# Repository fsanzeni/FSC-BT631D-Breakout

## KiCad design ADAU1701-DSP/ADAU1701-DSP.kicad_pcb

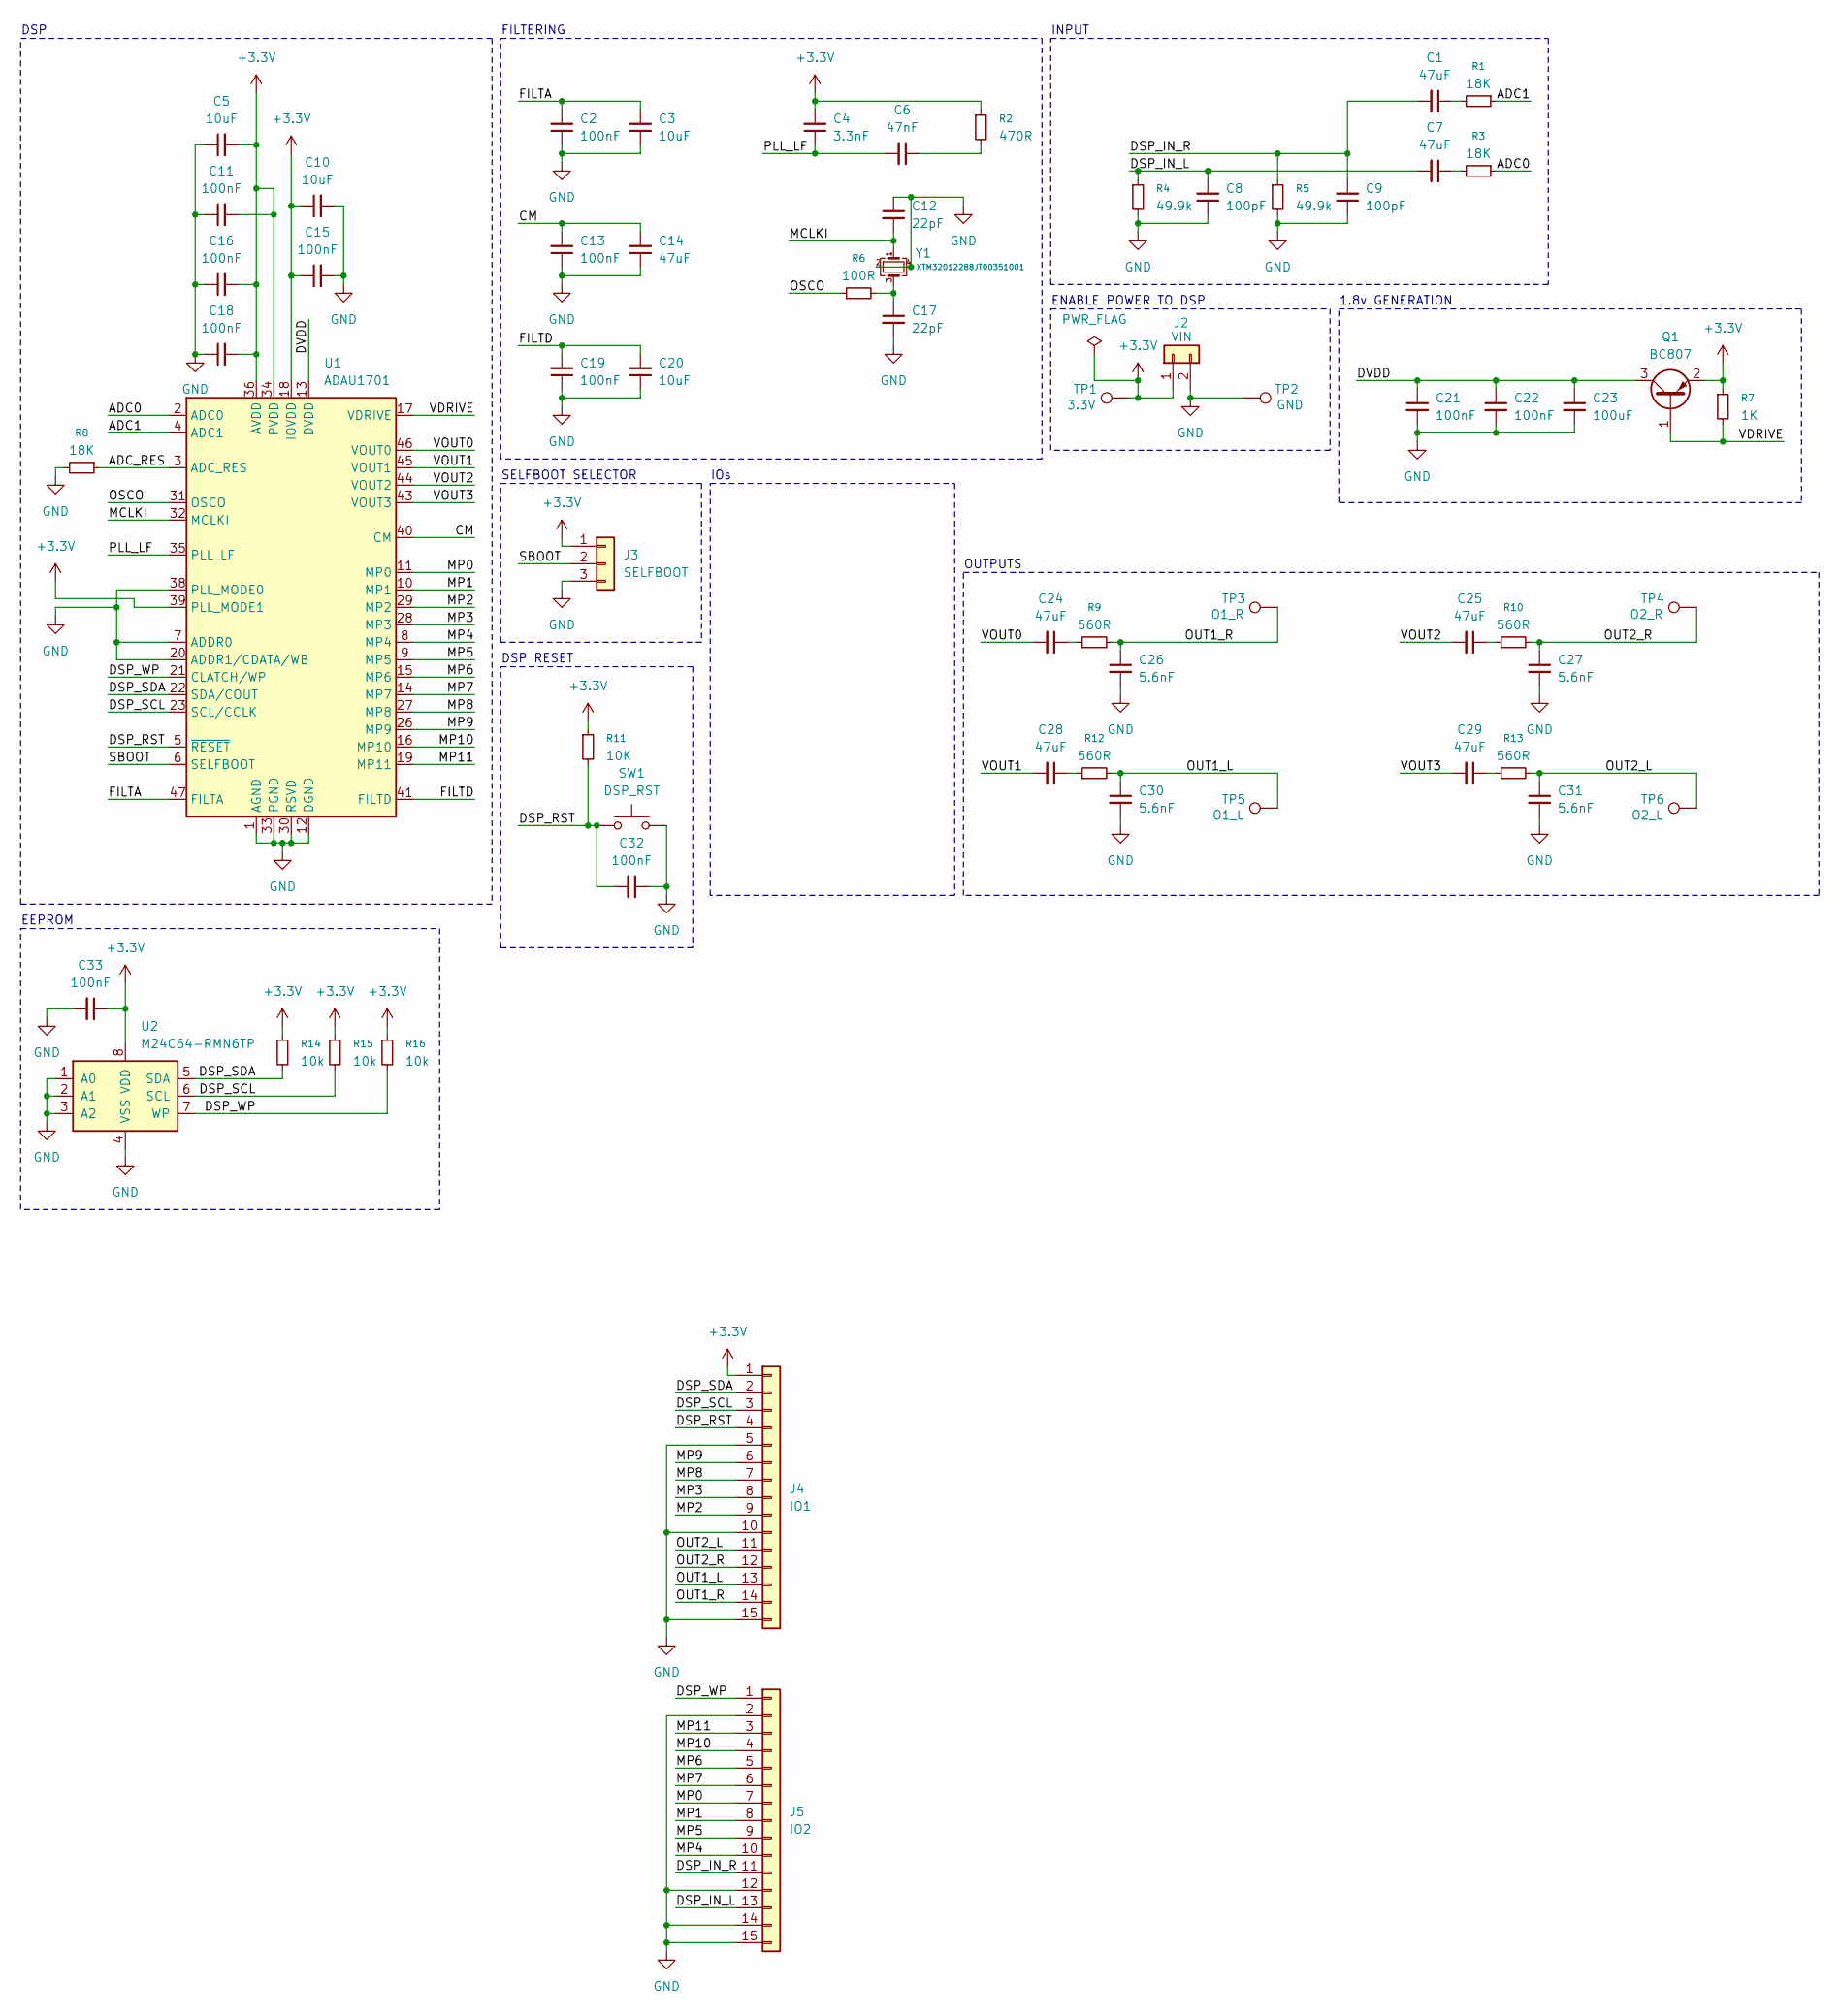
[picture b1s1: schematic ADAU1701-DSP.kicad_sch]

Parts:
C1, C7, C14, C24, C25, C28, C29: 47uF; C_0603_1608Metric_Pad1.08x0.95mm_HandSolder
C2, C11, C13, C15, C16, C18, C19, C21, C22, C32, C33: 100nF; C_0603_1608Metric_Pad1.08x0.95mm_HandSolder
C3, C5, C10, C20: 10uF; C_0603_1608Metric_Pad1.08x0.95mm_HandSolder
C4: 3.3nF; C_0603_1608Metric_Pad1.08x0.95mm_HandSolder
C6: 47nF; C_0603_1608Metric_Pad1.08x0.95mm_HandSolder
C8, C9: 100pF; C_0603_1608Metric_Pad1.08x0.95mm_HandSolder
C12, C17: 22pF; C_0603_1608Metric_Pad1.08x0.95mm_HandSolder
C23: 100uF; C_0603_1608Metric_Pad1.08x0.95mm_HandSolder
C26, C27, C30, C31: 5.6nF; C_0603_1608Metric_Pad1.08x0.95mm_HandSolder
J2: VIN; PinSocket_1x02_P2.54mm_Vertical
J3: SELFBOOT; PinHeader_1x03_P2.54mm_Vertical
J4: IO1; PinSocket_1x15_P2.54mm_Vertical
J5: IO2; PinSocket_1x15_P2.54mm_Vertical
Q1: BC807; SOT-23
R1, R3, R8: 18K; R_0603_1608Metric_Pad0.98x0.95mm_HandSolder
R2: 470R; R_0603_1608Metric_Pad0.98x0.95mm_HandSolder
R4, R5: 49.9k; R_0603_1608Metric_Pad0.98x0.95mm_HandSolder
R6: 100R; R_0603_1608Metric_Pad0.98x0.95mm_HandSolder
R7: 1K; R_0603_1608Metric_Pad0.98x0.95mm_HandSolder
R9, R10, R12, R13: 560R; R_0603_1608Metric_Pad0.98x0.95mm_HandSolder
R11: 10K; R_0603_1608Metric_Pad0.98x0.95mm_HandSolder
R14, R15, R16: 10k; R_0603_1608Metric_Pad0.98x0.95mm_HandSolder
SW1: DSP_RST; TS3425BA
TP1: 3.3V; TestPoint_THTPad_1.0x1.0mm_Drill0.5mm
TP2: GND; TestPoint_THTPad_1.0x1.0mm_Drill0.5mm
TP3: O1_R; TestPoint_THTPad_1.0x1.0mm_Drill0.5mm
TP4: O2_R; TestPoint_THTPad_1.0x1.0mm_Drill0.5mm
TP5: O1_L; TestPoint_THTPad_1.0x1.0mm_Drill0.5mm
TP6: O2_L; TestPoint_THTPad_1.0x1.0mm_Drill0.5mm
U1: ADAU1701; LQFP-48_7x7mm_P0.5mm
U2: M24C64-RMN6TP; SOIC-8_3.9x4.9mm_P1.27mm
Y1: XTM32012288JT00351001; Crystal_SMD_3225-4Pin_3.2x2.5mm_HandSoldering

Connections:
+3.3V: C4.2, C5.2, C10.1, C11.2, C15.1, C16.2, C18.2, C33.1, J2.1, J3.1, J4.1, Q1.2 (E), R2.1, R7.1, R11.1, R14.1, R15.1, R16.1, TP1.1, U1.18 (IOVDD), U1.34 (PVDD), U1.36 (AVDD), U1.39 (PLL_MODE1), U1.48 (AVDD), U2.8 (VDD)
/ADC0: R3.1, U1.2 (ADC0)
/ADC1: R1.1, U1.4 (ADC1)
/ADC_RES: R8.1, U1.3 (ADC_RES)
/CM: C13.2, C14.2, U1.40 (CM)
/DSP_IN_L: C7.2, C8.2, J5.13, R4.1
/DSP_IN_R: C1.2, C9.2, J5.11, R5.1
/DSP_RST: C32.2, J4.4, R11.2, SW1.1, U1.5 (~RESET)
/DSP_SCL: J4.3, R15.2, U1.23 (SCL/CCLK), U2.6 (SCL)
/DSP_SDA: J4.2, R14.2, U1.22 (SDA/COUT), U2.5 (SDA)
/DSP_WP: J5.1, R16.2, U1.21 (CLATCH/WP), U2.7 (WP)
/DVDD: C21.1, C22.1, C23.1, Q1.3 (C), U1.13 (DVDD), U1.24 (DVDD)
/FILTA: C2.2, C3.2, U1.47 (FILTA)
/FILTD: C19.2, C20.2, U1.41 (FILTD)
/MCLKI: C12.2, U1.32 (MCLKI), Y1.1
/MP0: J5.7, U1.11 (MP0)
/MP1: J5.8, U1.10 (MP1)
/MP2: J4.9, U1.29 (MP2)
/MP3: J4.8, U1.28 (MP3)
/MP4: J5.10, U1.8 (MP4)
/MP5: J5.9, U1.9 (MP5)
/MP6: J5.5, U1.15 (MP6)
/MP7: J5.6, U1.14 (MP7)
/MP8: J4.7, U1.27 (MP8)
/MP9: J4.6, U1.26 (MP9)
/MP10: J5.4, U1.16 (MP10)
/MP11: J5.3, U1.19 (MP11)
/OSCO: R6.1, U1.31 (OSCO)
/OUT1_L: C30.1, J4.13, R12.2, TP5.1
/OUT1_R: C26.1, J4.14, R9.2, TP3.1
/OUT2_L: C31.1, J4.11, R13.2, TP6.1
/OUT2_R: C27.1, J4.12, R10.2, TP4.1
/PLL_LF: C4.1, C6.2, U1.35 (PLL_LF)
/SBOOT: J3.2, U1.6 (SELFBOOT)
/VDRIVE: Q1.1 (B), R7.2, U1.17 (VDRIVE)
/VOUT0: C24.2, U1.46 (VOUT0)
/VOUT1: C28.2, U1.45 (VOUT1)
/VOUT2: C25.2, U1.44 (VOUT2)
/VOUT3: C29.2, U1.43 (VOUT3)
GND: C2.1, C3.1, C5.1, C8.1, C9.1, C10.2, C11.1, C12.1, C13.1, C14.1, C15.2, C16.1, C17.2, C18.1, C19.1, C20.1, C21.2, C22.2, C23.2, C26.2, C27.2, C30.2, C31.2, C32.1, C33.2, J2.2, J3.3, J4.5, J4.10, J4.15, J5.2, J5.12, J5.14, J5.15, R4.2, R5.2, R8.2, SW1.2, TP2.1, U1.1 (AGND), U1.7 (ADDR0), U1.12 (DGND), U1.20 (ADDR1/CDATA/WB), U1.25 (DGND), U1.30 (RSVD), U1.33 (PGND), U1.37 (AGND), U1.38 (PLL_MODE0), U1.42 (AGND), U2.1 (A0), U2.2 (A1), U2.3 (A2), U2.4 (VSS), Y1.2, Y1.4
unnamed: C1.1, R1.2
unnamed: C6.1, R2.2
unnamed: C7.1, R3.2
unnamed: C17.1, R6.2, Y1.3
unnamed: C24.1, R9.1
unnamed: C25.1, R10.1
unnamed: C28.1, R12.1
unnamed: C29.1, R13.1

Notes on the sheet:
EEPROM
INPUT
DSP RESET
FILTERING
DSP
IOs
SELFBOOT SELECTOR
ENABLE POWER TO DSP
1.8v GENERATION
OUTPUTS

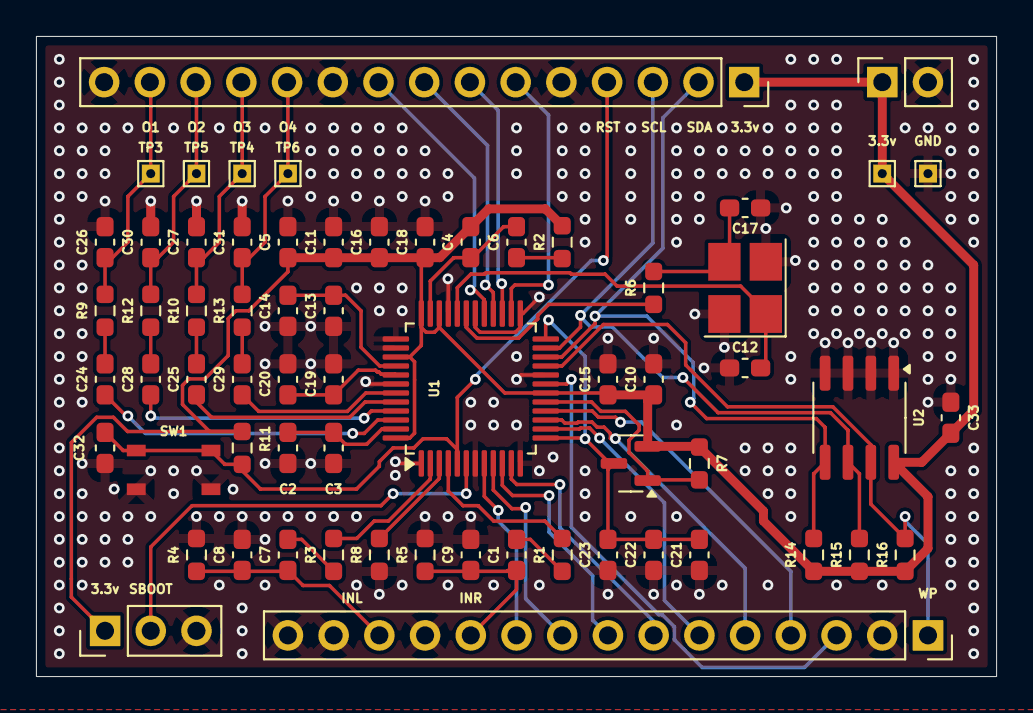
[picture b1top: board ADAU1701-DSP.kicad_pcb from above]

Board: 2 copper layers, 53.3 x 35.6 mm, 64 parts (0 on the bottom side), 48 nets.

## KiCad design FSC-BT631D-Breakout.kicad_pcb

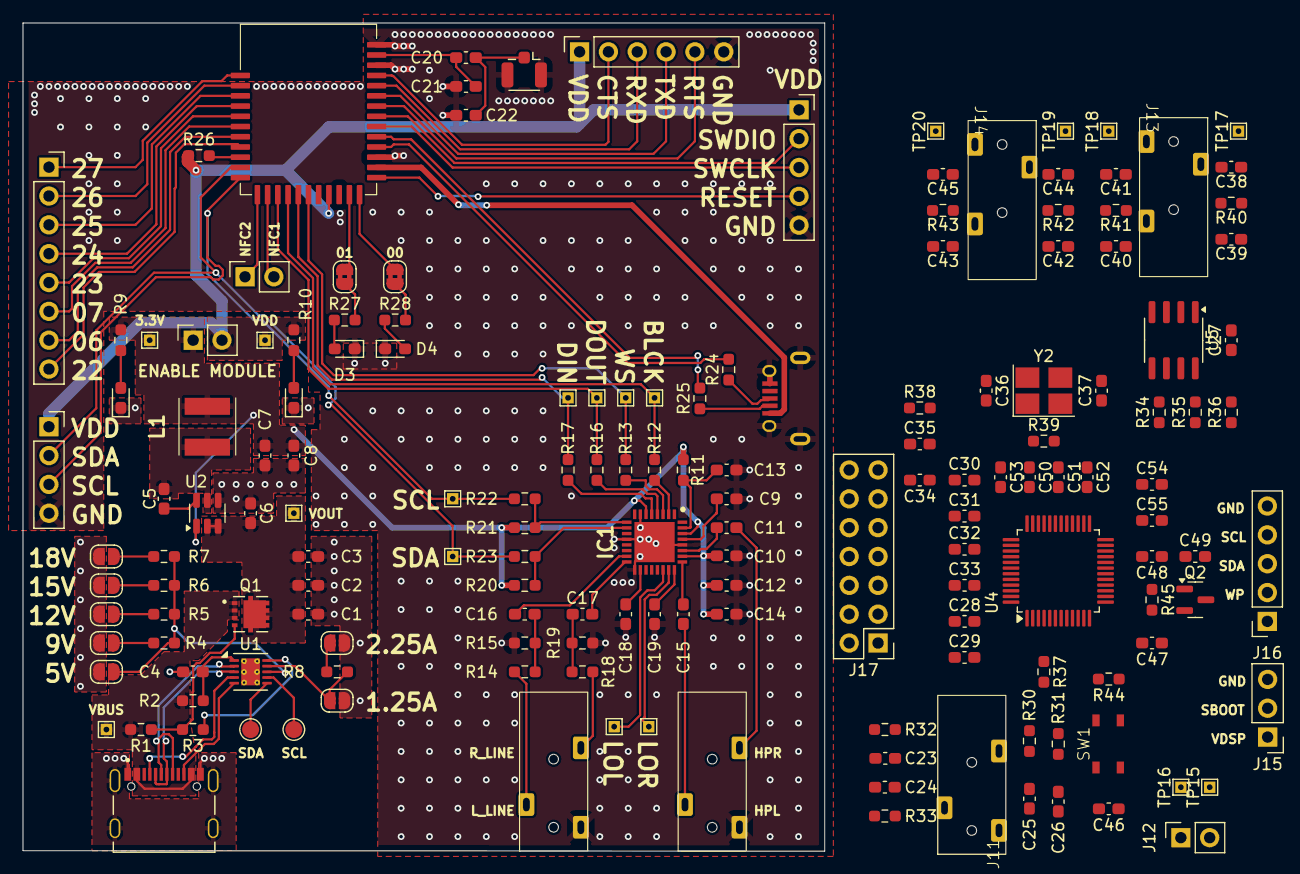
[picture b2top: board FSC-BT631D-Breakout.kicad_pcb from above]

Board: 2 copper layers, 70.6 x 72.9 mm, 161 parts (0 on the bottom side), 128 nets.

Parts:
AE1: Antenna_Shield; U.FL_Hirose_U.FL-R-SMT-1_Vertical
C1, C2, C3, C6, C11, C15, C16, C17, C19: 4.7uF; C_0603_1608Metric_Pad1.08x0.95mm_HandSolder
C4: 1uF/50V; C_0603_1608Metric_Pad1.08x0.95mm_HandSolder
C5: 0.1uF; C_0603_1608Metric_Pad1.08x0.95mm_HandSolder
C7, C8: 22uF; C_0603_1608Metric_Pad1.08x0.95mm_HandSolder
C9, C10, C18, C29, C33, C53, C54: 10uF; C_0603_1608Metric_Pad1.08x0.95mm_HandSolder
C12: 1uF; C_0603_1608Metric_Pad1.08x0.95mm_HandSolder
C13: 220nF; C_0603_1608Metric_Pad1.08x0.95mm_HandSolder
C14, C27, C28, C30, C32, C46, C47, C48, C50, C51, C52, C55: 100nF; C_0603_1608Metric_Pad1.08x0.95mm_HandSolder
C20, C21, C22: NC; C_0603_1608Metric_Pad1.08x0.95mm_HandSolder
C23, C24: 100pF; C_0603_1608Metric_Pad1.08x0.95mm_HandSolder
C25, C26, C31, C39, C40, C42, C43: 47uF; C_0603_1608Metric_Pad1.08x0.95mm_HandSolder
C34: 3.3nF; C_0603_1608Metric_Pad1.08x0.95mm_HandSolder
C35: 47nF; C_0603_1608Metric_Pad1.08x0.95mm_HandSolder
C36, C37: 22pF; C_0603_1608Metric_Pad1.08x0.95mm_HandSolder
C38, C41, C44, C45: 5.6nF; C_0603_1608Metric_Pad1.08x0.95mm_HandSolder
C49: 100uF; C_0603_1608Metric_Pad1.08x0.95mm_HandSolder
D1: 3.3V; LED_0603_1608Metric_Pad1.05x0.95mm_HandSolder
D2: VDD; LED_0603_1608Metric_Pad1.05x0.95mm_HandSolder
D3: LED1; LED_0603_1608Metric_Pad1.05x0.95mm_HandSolder
D4: LED2; LED_0603_1608Metric_Pad1.05x0.95mm_HandSolder
IC1: TLV320AIC3204IRHBR; QFN50P500X500X100-33N-D
J1: USB_C_Receptacle_USB2.0_16P; SHOUHAN_TYPE-C_16PIN_2MD__073
J2: M_EN; PinSocket_1x02_P2.54mm_Vertical
J3: LINE IN; XKB_PJ-3200
J4: LINE OUT; XKB_PJ-3200
J5: USB_B_Micro; KH-MICRO5P-JN
J6: UPDATE; PinSocket_1x05_P2.54mm_Vertical
J7: UART; PinSocket_1x06_P2.54mm_Vertical
J8: I2C; PinSocket_1x04_P2.54mm_Vertical
J9: NFC; PinSocket_1x02_P2.54mm_Vertical
J10: PIO; PinSocket_1x08_P2.54mm_Vertical
J11: DSP IN; XKB_PJ-3200
J12: DSP_EN; PinSocket_1x02_P2.54mm_Vertical
J13: OUT1; XKB_PJ-3200
J14: OUT2; XKB_PJ-3200
J15: SELFBOOT; PinHeader_1x03_P2.54mm_Vertical
J16: DSP_PROG; PinSocket_1x05_P2.54mm_Vertical
J17: DSP_GPIO; PinHeader_2x07_P2.54mm_Vertical
JP1: 5V; SolderJumper-2_P1.3mm_Open_RoundedPad1.0x1.5mm
JP2: 9V; SolderJumper-2_P1.3mm_Open_RoundedPad1.0x1.5mm
JP3: 12V; SolderJumper-2_P1.3mm_Open_RoundedPad1.0x1.5mm
JP4: 15V; SolderJumper-2_P1.3mm_Open_RoundedPad1.0x1.5mm
JP5: 1.25A; SolderJumper-2_P1.3mm_Open_RoundedPad1.0x1.5mm
JP6: 18V; SolderJumper-2_P1.3mm_Open_RoundedPad1.0x1.5mm
JP7: 2.25A; SolderJumper-2_P1.3mm_Open_RoundedPad1.0x1.5mm
JP8: LED1_S; SolderJumper-2_P1.3mm_Bridged2Bar_RoundedPad1.0x1.5mm
JP9: LED2_S; SolderJumper-2_P1.3mm_Bridged2Bar_RoundedPad1.0x1.5mm
L1: 10uH; VLS5045EX330M
Q1: AONR21307
Q2: BC807; SOT-23
R1: 49.9K; R_0603_1608Metric_Pad0.98x0.95mm_HandSolder
R2: 10R; R_0603_1608Metric_Pad0.98x0.95mm_HandSolder
R3: 5.1K; R_0603_1608Metric_Pad0.98x0.95mm_HandSolder
R4: 6K; R_0603_1608Metric_Pad0.98x0.95mm_HandSolder
R5, R14, R18, R44: 10K; R_0603_1608Metric_Pad0.98x0.95mm_HandSolder
R6, R8: 14K; R_0603_1608Metric_Pad0.98x0.95mm_HandSolder
R7, R30, R31, R37: 18K; R_0603_1608Metric_Pad0.98x0.95mm_HandSolder
R9, R10, R27, R28, R45: 1K; R_0603_1608Metric_Pad0.98x0.95mm_HandSolder
R11: 220K; R_0603_1608Metric_Pad0.98x0.95mm_HandSolder
R12, R13, R16, R17, R26: 0R; R_0603_1608Metric_Pad0.98x0.95mm_HandSolder
R15, R19, R20, R21: 4.7K; R_0603_1608Metric_Pad0.98x0.95mm_HandSolder
R22, R23: 33R; R_0603_1608Metric_Pad0.98x0.95mm_HandSolder
R24, R25: 22R; R_0603_1608Metric_Pad0.98x0.95mm_HandSolder
R32, R33: 49.9k; R_0603_1608Metric_Pad0.98x0.95mm_HandSolder
R34, R35, R36: 10k; R_0603_1608Metric_Pad0.98x0.95mm_HandSolder
R38: 470R; R_0603_1608Metric_Pad0.98x0.95mm_HandSolder
R39: 100R; R_0603_1608Metric_Pad0.98x0.95mm_HandSolder
R40, R41, R42, R43: 560R; R_0603_1608Metric_Pad0.98x0.95mm_HandSolder
SW1: DSP_RST; TS3425BA
TP1: VBUS; TestPoint_THTPad_1.0x1.0mm_Drill0.5mm
TP2: SCL; TestPoint_Pad_D1.5mm
TP3: SDA; TestPoint_Pad_D1.5mm
TP4: VOUT; TestPoint_THTPad_1.0x1.0mm_Drill0.5mm
TP5, TP16: 3.3V; TestPoint_THTPad_1.0x1.0mm_Drill0.5mm
TP6: VDD; TestPoint_THTPad_1.0x1.0mm_Drill0.5mm
TP7: BLCK; TestPoint_THTPad_1.0x1.0mm_Drill0.5mm
TP8: WS; TestPoint_THTPad_1.0x1.0mm_Drill0.5mm
TP9: DOUT; TestPoint_THTPad_1.0x1.0mm_Drill0.5mm
TP10: LOR; TestPoint_THTPad_1.0x1.0mm_Drill0.5mm
TP11: DIN; TestPoint_THTPad_1.0x1.0mm_Drill0.5mm
TP12: LOL; TestPoint_THTPad_1.0x1.0mm_Drill0.5mm
TP13: SCL; TestPoint_THTPad_1.0x1.0mm_Drill0.5mm
TP14: SDA; TestPoint_THTPad_1.0x1.0mm_Drill0.5mm
TP15: V_DSP; TestPoint_THTPad_1.0x1.0mm_Drill0.5mm
TP17: O1_R; TestPoint_THTPad_1.0x1.0mm_Drill0.5mm
TP18: O1_L; TestPoint_THTPad_1.0x1.0mm_Drill0.5mm
TP19: O2_R; TestPoint_THTPad_1.0x1.0mm_Drill0.5mm
TP20: O2_L; TestPoint_THTPad_1.0x1.0mm_Drill0.5mm
U1: HUSB238_002DD; DFN-10-1EP_3x3mm_P0.5mm_EP1.65x2.38mm_ThermalVias
U2: AP63203WU-7; TSOT-23-6
U3: FSC-BT631D
U4: ADAU1701; LQFP-48_7x7mm_P0.5mm
U5: M24C64-RMN6TP; SOIC-8_3.9x4.9mm_P1.27mm
Y2: XTM32012288JT00351001; Crystal_SMD_3225-4Pin_3.2x2.5mm_HandSoldering

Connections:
+3.3V: C7.2, C8.2, C10.1, C12.1, C14.1, IC1.6 (IOVDD), IC1.26 (LDOIN), IC1.30 (LDO__SELECT), J2.1, J12.1, L1.2, R9.2, R11.2, R20.1, R21.1, TP5.1, TP16.1, U2.1 (FB)
+5V: J5.1 (VBUS), U3.24 (VBUS)
/DSP/ADC0: R30.1, U4.2 (ADC0)
/DSP/ADC1: R31.1, U4.4 (ADC1)
/DSP/ADC_RES: R37.1, U4.3 (ADC_RES)
/DSP/CM: C30.2, C31.2, U4.40 (CM)
/DSP/DSP_IN_LEFT: C23.2, C25.2, J11.T, R32.1
/DSP/DSP_IN_RIGHT: C24.2, C26.2, J11.S, R33.1
/DSP/DSP_RST: C46.2, J16.1, R44.2, SW1.1, U4.5 (~RESET)
/DSP/DSP_SCL: J16.4, R35.2, U4.23 (SCL/CCLK), U5.6 (SCL)
/DSP/DSP_SDA: J16.3, R34.2, U4.22 (SDA/COUT), U5.5 (SDA)
/DSP/DSP_WP: J16.2, R36.2, U4.21 (CLATCH/WP), U5.7 (WP)
/DSP/DVDD: C47.1, C48.1, C49.1, Q2.3 (C), U4.13 (DVDD), U4.24 (DVDD)
/DSP/FILTA: C28.2, C29.2, U4.47 (FILTA)
/DSP/FILTD: C32.2, C33.2, U4.41 (FILTD)
/DSP/MCLKI: C36.2, U4.32 (MCLKI), Y2.1
/DSP/MP0: J17.1, U4.11 (MP0)
/DSP/MP1: J17.2, U4.10 (MP1)
/DSP/MP2: J17.3, U4.29 (MP2)
/DSP/MP3: J17.4, U4.28 (MP3)
/DSP/MP4: J17.5, U4.8 (MP4)
/DSP/MP5: J17.6, U4.9 (MP5)
/DSP/MP6: J17.7, U4.15 (MP6)
/DSP/MP7: J17.8, U4.14 (MP7)
/DSP/MP8: J17.9, U4.27 (MP8)
/DSP/MP9: J17.10, U4.26 (MP9)
/DSP/MP10: J17.11, U4.16 (MP10)
/DSP/MP11: J17.12, U4.19 (MP11)
/DSP/OSCO: R39.1, U4.31 (OSCO)
/DSP/OUT1_LEFT: C41.1, J13.T, R41.2, TP18.1
/DSP/OUT1_RIGHT: C38.1, J13.S, R40.2, TP17.1
/DSP/OUT2_LEFT: C45.1, J14.T, R43.2, TP20.1
/DSP/OUT2_RIGHT: C44.1, J14.S, R42.2, TP19.1
/DSP/PLL_LF: C34.1, C35.2, U4.35 (PLL_LF)
/DSP/SBOOT: J15.2, U4.6 (SELFBOOT)
/DSP/VDRIVE: Q2.1 (B), R45.2, U4.17 (VDRIVE)
/DSP/VOUT0: C39.2, U4.46 (VOUT0)
/DSP/VOUT1: C40.2, U4.45 (VOUT1)
/DSP/VOUT2: C42.2, U4.44 (VOUT2)
/DSP/VOUT3: C43.2, U4.43 (VOUT3)
/codec/AVDD: C19.1, IC1.24 (AVDD)
/codec/I2S2_CLK: IC1.2 (BCLK), R12.2
/codec/I2S2_DI: IC1.5 (DOUT_/_MFP2), R17.2
/codec/I2S2_DO: IC1.4 (DIN_/_MFP1), R16.2
/codec/I2S2_WS: IC1.3 (WCLK), R13.2
/module/MOD_D+: J5.3 (D+), R24.1
/module/MOD_D-: J5.2 (D-), R25.1
/module/USB_D+: R24.2, U3.26 (USB_D+)
/module/USB_D-: R25.2, U3.27 (USB_D-)
/power/BST: C5.2, U2.6 (BST)
/power/CC1: J1.A5 (CC1), U1.4 (CC1)
/power/CC2: J1.B5 (CC2), U1.5 (CC2)
/power/D+: J1.A6 (D+), J1.B6 (D+), U1.2 (D+)
/power/D-: J1.A7 (D-), J1.B7 (D-), U1.3 (D-)
/power/ISET: JP5.1 (A), R8.1, U1.9 (ISET)
/power/SCL: TP2.1, U1.7 (SCL)
/power/SDA: TP3.1, U1.6 (SDA)
/power/SW: C5.1, L1.1, U2.5 (SW)
/power/VOUT: C1.2, C2.2, C3.2, C6.2, Q1.5_6_7_8, TP4.1, U2.2 (EN), U2.3 (IN)
/power/VSET: JP1.1 (A), R4.1, R5.1, R6.1, R7.1, U1.8 (VSET)
GND: AE1.2 (Shield), C1.1, C2.1, C3.1, C4.1, C6.1, C7.1, C8.1, C9.2, C10.2, C12.2, C13.1, C14.2, C18.2, C19.2, C21.1, C22.1, C23.1, C24.1, C27.2, C28.1, C29.1, C30.1, C31.1, C32.1, C33.1, C36.1, C37.2, C38.2, C41.2, C44.2, C45.2, C46.1, C47.2, C48.2, C49.2, C50.1, C51.1, C52.1, C53.1, C54.2, C55.2, D1.1 (K), D2.1 (K), D3.1 (K), D4.1 (K), IC1.7 (IOVSS), IC1.12 (SPI__SELECT), IC1.17 (AVSS), IC1.28 (DVSS), IC1.33 (EP), J1.A1 (GND), J1.S1 (SHIELD), J3.G, J4.G, J5.5 (GND), J5.6 (Shield), J6.5, J7.6, J8.4, J11.G, J13.G, J14.G, J15.3, J16.5, J17.13, J17.14, JP1.2 (B), JP2.2 (B), JP3.2 (B), JP4.2 (B), JP5.2 (B), JP6.2 (B), JP7.2 (B), R15.2, R19.2, R32.2, R33.2, R37.2, SW1.2, U1.11 (GND), U2.4 (GND), U3.20 (GND), U3.25 (GND), U3.34 (GND), U3.36 (GND), U4.1 (AGND), U4.7 (ADDR0), U4.12 (DGND), U4.20 (ADDR1/CDATA/WB), U4.25 (DGND), U4.30 (RSVD), U4.33 (PGND), U4.37 (AGND), U4.38 (PLL_MODE0), U4.42 (AGND), U5.1 (A0), U5.2 (A1), U5.3 (A2), U5.4 (VSS), Y2.2, Y2.4
HPL: C15.2, J4.S
HPR: C11.2, J4.T
L_LINE2: C16.2, IC1.15 (IN2_L)
unnamed: C16.1, R14.1, R15.1
unnamed: C17.1, R18.1, R19.1
unnamed: C20.1, C21.2, U3.35 (RF)
unnamed: AE1.1 (A), C20.2, C22.2
unnamed: C25.1, R30.2
unnamed: C26.1, R31.2
unnamed: C35.1, R38.2
unnamed: C37.1, R39.2, Y2.3
unnamed: C39.1, R40.1
unnamed: C40.1, R41.1
unnamed: C42.1, R42.1
unnamed: C43.1, R43.1
unnamed: D1.2 (A), R9.1
unnamed: D2.2 (A), R10.1
unnamed: D3.2 (A), R27.1
unnamed: C9.1, IC1.29 (DVDD)
unnamed: C15.1, IC1.25 (HPL)
unnamed: C11.1, IC1.27 (HPR)
unnamed: IC1.22 (LOL), TP12.1
unnamed: IC1.23 (LOR), TP10.1
unnamed: C18.1, IC1.18 (REF)
unnamed: IC1.9 (SCL/~SS), R21.2, R22.2
unnamed: IC1.10 (SDA/MOSI), R20.2, R23.2
unnamed: C13.2, IC1.31 (~RESET), R11.1
unnamed: J3.S, R14.2
unnamed: J3.T, R18.2
unnamed: JP2.1 (A), R4.2
unnamed: JP3.1 (A), R5.2
unnamed: JP4.1 (A), R6.2
unnamed: JP6.1 (A), R7.2
unnamed: JP7.1 (A), R8.2
unnamed: JP9.1 (A), R28.2
unnamed: Q1.4, R1.1, R3.2
unnamed: R3.1, U1.10 (GATE)
unnamed: C4.2, R2.1, U1.1 (VIN)
P0.02/NFC1: J9.2, U3.13 (P0.02/NFC1)
P0.03/NFC2: J9.1, U3.12 (P0.03/NFC2)
P0.06: J10.7, U3.7 (P0.06)
P0.07: J10.6, U3.6 (P0.07)
P0.13/I2S_DIN: R17.1, TP11.1, U3.16 (P0.13/I2S_IN)
P0.14/I2S_BCLK: R12.1, TP7.1, U3.15 (P0.14/I2S_CLK)
P0.15/I2S_DOUT: R16.1, TP9.1, U3.14 (P0.15/I2S_OUT)
P0.16/I2S_WS: R13.1, TP8.1, U3.17 (P0.16/I2S_SYNC)
P0.22: J10.8, U3.8 (P0.22)
P0.23: J10.5, U3.5 (P0.23)
P0.24: J10.4, U3.4 (P0.24)
P0.25: J10.3, U3.3 (P0.25)
P0.26: J10.2, U3.2 (P0.26)
P0.27: J10.1, U3.1 (P0.27)
P1.00: JP9.2 (B), U3.22 (P1.00)
P1.01: JP8.2 (B), U3.21 (P1.01)
P1.1/UART_RTS: J7.5, U3.30 (P1.11/UART_RTS)
P1.02/I2C_SDA: J8.2, R23.1, TP14.1, U3.10 (P1.02/SDA)
P1.03/I2C_SCL: J8.3, R22.1, TP13.1, U3.11 (P0.03/SCL)
P1.08/UART_RXD: J7.3, U3.32 (P1.08/UART_RXD)
P1.09/UART_TXD: J7.4, U3.31 (P1.09/UART_TXD)
P1.10/UART_CTS: J7.2, U3.33 (P1.10/UART_CTS_N)
RESET: J6.4, U3.23 (RESET)
R_LINE2: C17.2, IC1.16 (IN2_R)
SWDCLK: J6.3, U3.28 (SDWCLK)
SWDIO: J6.2, U3.29 (SWDIO)
VBUS: J1.A4 (VBUS), Q1.1, Q1.2, Q1.3, R1.2, R2.2, TP1.1
VDD: J2.2, J6.1, J7.1, J8.1, R10.2, R26.1, TP6.1, U3.19 (VDD)
V_DSP: C27.1, C34.2, C50.2, C51.2, C52.2, C53.2, C54.1, C55.1, J12.2, J15.1, Q2.2 (E), R34.1, R35.1, R36.1, R38.1, R44.1, R45.1, TP15.1, U4.18 (IOVDD), U4.34 (PVDD), U4.36 (AVDD), U4.39 (PLL_MODE1), U4.48 (AVDD), U5.8 (VDD)

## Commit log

2025-04-30 added power schematic, gitignore
2025-04-30 power section done
2025-05-12 schematic completed
2025-05-18 FINALISED LAYOUT
2025-05-18 fixed silkscreen
2025-05-20 fixed ground pour
2025-05-21 added ibom & fabrication files
2025-05-21 added dsp schematic
2025-05-21 initial routing
2025-05-21 folder restructure
2025-05-22 dsp routing finished
